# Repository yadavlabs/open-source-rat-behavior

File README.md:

# open-source-rat-behavior
Open source software for controlling operant conditioning chambers, running behavioral experiments, and collecting data. 

# IMPORTANT: This branch is a work in progress which now uses Docker for building and deploying the app. This README has not yet been updated to reflect these changes.

## Prerequisites
For specific version see `docs\Software Versions.xlsx`
- `Python` If using standalone [Python version](https://www.python.org/downloads/release/python-3810/), during installation check "Add python.exe to PATH"
- `Git` Can be downloaded from [here](https://git-scm.com/downloads/win)
- `Node.js` Can be downloaded from [here](https://nodejs.org/en/download). Do not check "Automatically install the necessary tools..."
- `Angular CLI`
    ```command
    >npm install -g @angular/cli@15.2.10
    >cd path\to\open-source-rat-behavior\Angular Files
    >ng add @angular/material
    ```

## Installation
1. Clone repository to your machine. 
2. Setup backend environment with `venv`
    - Choose or create a folder to store the environment
    - Open command terminal and run the following to create and activate the environment:
    ```command
    >cd path\to\open-source-rat-behavior\Flask Project Files\pythonBackend
    >python -m venv .venv
    >.venv\Scripts\activate.bat
    ```
    Note: While not necessary, it is best to have the environment folder in the `Flask Project Files\pythonBackend` directory and the environment named `.venv`

    - if the setup was successful, the command prompt will look like:
    ```command
    (.venv) C:\Users\...\open-source-rat-behavior>
    ```
    - (Optional) Upgrade pip and managing modules:
    ```command
    >python -m pip install --upgrade pip setuptools wheel
    ```
    - Install required modules in `requirements.txt` inside virtual environment:
    ```command
    >cd path\to\open-source-rat-behavior
    >pip install -r requirements.txt
    ```
    - To deactivate environment run:
    ```command
    >behavior-chamber-env\Scripts\deactivate.bat
    ```
    - Set name of Flask application (must be run on each usage unless `setx` is used):
    ```command
    >cd path\to\open-source-rat-behavior\Flask Project Files\pythonBackend
    >set FLASK_APP=application.py
    >set FLASK_DEBUG=true
    ```
3. Alternatively, setup backend environment with `conda`
    - In Anaconda Prompt:
    ```command
    >conda create -n behavior-chamber-env python=3.8
    >conda activate behavior-chamber-env
    >cd path\to\open-source-rat-behavior
    >pip install -r requirements.txt
    ```

## Launch Python Backend
1. Open command terminal.
2. Activate environment:
```command
>cd path\to\environment\folder
>behavior-chamber-env\Scripts\activate.bat
```
3. Navigate to the directory containing the file "application.py" and run app:
```command
>cd path\to\open-source-rat-behavior\Flask Project Files\pythonBackend
>flask run
```
Note: You don't need to open the URL (e.g. `http://127.0.0.1:5000`), but you can if you want

## Launch Angular App
1. Open a second command terminal.
2. Navigate to the diretory containing the folders "src", ".angular", etc. 
```command
>cd path\to\open-source-rat-behavior\Angular Files
```
3. Launch app:
```command
>ng serve --o
```
Note: The "--o" flag should open the application for you once it compiles. REMINDER THAT YOU NEED NODE.JS AND GIT INSTALLED, perhaps even Angular CLI.
You don't need Visual Studios unless you intend to modify code

## Launch Frontend and Backend with batch script
Instead of manually opening two terminals to start the app, two batch files are available to launch the frontend and backend automatically

1. `start-full.bat`
    - Run if the Python environment was setup with `venv`
    - Assumes the virtual environment is named `.venv` and is located in:
        `\Flask Project Files\pythonBackend\.venv`
    - If this is not the case update the following in the script:
        - `ENV_NAME`
        - `ENV_DIR`

2. `start-full-conda.bat`
    - Run if the Python environment was setup with `conda`
    - Assumes name of environment is `behavior-chamber-env` and Anaconda installation is `%USERPROFILE%\anaconda3\condabin\`
    - If this is not the case update the following in the script:
        - `ENV_NAME`
        - `ENV_DIR`

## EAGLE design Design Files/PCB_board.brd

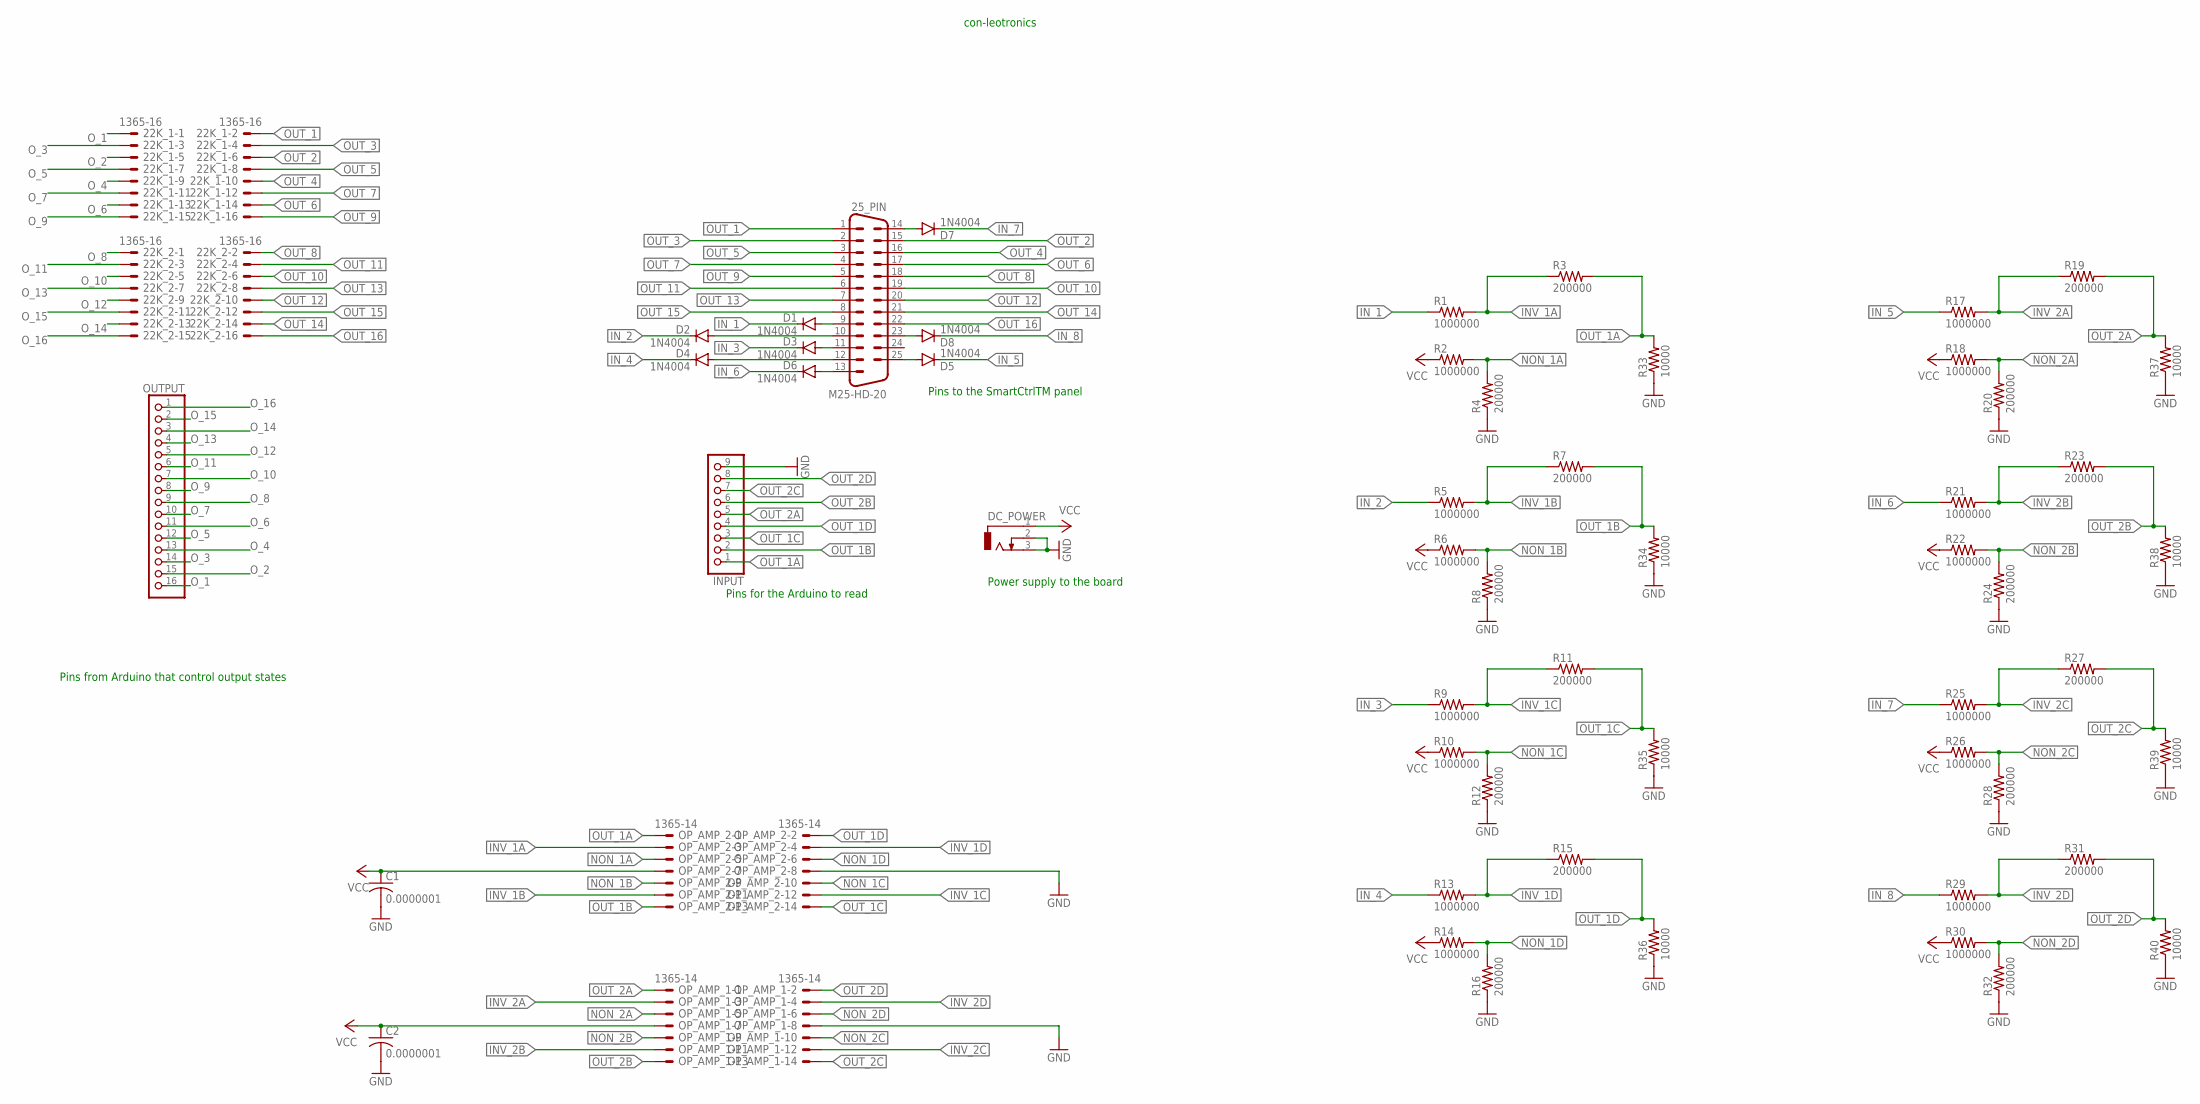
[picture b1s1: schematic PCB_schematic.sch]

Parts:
22K_1, 22K_2: 1365-16
25_PIN: M25-HD-20
C1, C2: 0.0000001; C1206
D1, D2, D3, D4, D5, D6, D7, D8: 1N4004; DO41-10
DC_POWER: DCJ0303
INPUT: PINHD-1X9; 1X09
OP_AMP_1, OP_AMP_2: 1365-14
OUTPUT: PINHD-1X16; 1X16
R1, R2, R5, R6, R9, R10, R13, R14, R17, R18, R21, R22, R25, R26, R29, R30: 1000000; R1206
R3, R4, R7, R8, R11, R12, R15, R16, R19, R20, R23, R24, R27, R28, R31, R32: 200000; R1206
R33, R34, R35, R36, R37, R38, R39, R40: 10000; R1206

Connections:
GND: C1.2, C2.2, DC_POWER.2, DC_POWER.3, INPUT.9, OP_AMP_1.8, OP_AMP_2.8, R4.1, R8.1, R12.1, R16.1, R20.1, R24.1, R28.1, R32.1, R33.1, R34.1, R35.1, R36.1, R37.1, R38.1, R39.1, R40.1
INV_1A: OP_AMP_2.3, R1.2, R3.1
INV_1B: OP_AMP_2.11, R5.2, R7.1
INV_1C: OP_AMP_2.12, R9.2, R11.1
INV_1D: OP_AMP_2.4, R13.2, R15.1
INV_2A: OP_AMP_1.3, R17.2, R19.1
INV_2B: OP_AMP_1.11, R21.2, R23.1
INV_2C: OP_AMP_1.12, R25.2, R27.1
INV_2D: OP_AMP_1.4, R29.2, R31.1
IN_1: D1.C, R1.1
IN_2: D2.C, R5.1
IN_3: D3.C, R9.1
IN_4: D4.C, R13.1
IN_5: D5.C, R17.1
IN_6: D6.C, R21.1
IN_7: D7.C, R25.1
IN_8: D8.C, R29.1
unnamed: 25_PIN.9, D1.A
unnamed: 25_PIN.10, D2.A
unnamed: 25_PIN.11, D3.A
unnamed: 25_PIN.12, D4.A
unnamed: 25_PIN.25, D5.A
unnamed: 25_PIN.13, D6.A
unnamed: 25_PIN.23, D8.A
unnamed: 25_PIN.14, D7.A
NON_1A: OP_AMP_2.5, R2.2, R4.2
NON_1B: OP_AMP_2.9, R6.2, R8.2
NON_1C: OP_AMP_2.10, R10.2, R12.2
NON_1D: OP_AMP_2.6, R14.2, R16.2
NON_2A: OP_AMP_1.5, R18.2, R20.2
NON_2B: OP_AMP_1.9, R22.2, R24.2
NON_2C: OP_AMP_1.10, R26.2, R28.2
NON_2D: OP_AMP_1.6, R30.2, R32.2
OUT_1: 22K_1.2, 25_PIN.1
OUT_1A: INPUT.1, OP_AMP_2.1, R3.2, R33.2
OUT_1B: INPUT.2, OP_AMP_2.13, R7.2, R34.2
OUT_1C: INPUT.3, OP_AMP_2.14, R11.2, R35.2
OUT_1D: INPUT.4, OP_AMP_2.2, R15.2, R36.2
OUT_2: 22K_1.6, 25_PIN.15
OUT_2A: INPUT.5, OP_AMP_1.1, R19.2, R37.2
OUT_2B: INPUT.6, OP_AMP_1.13, R23.2, R38.2
OUT_2C: INPUT.7, OP_AMP_1.14, R27.2, R39.2
OUT_2D: INPUT.8, OP_AMP_1.2, R31.2, R40.2
OUT_3: 22K_1.4, 25_PIN.2
OUT_4: 22K_1.10, 25_PIN.16
OUT_5: 22K_1.8, 25_PIN.3
OUT_6: 22K_1.14, 25_PIN.17
OUT_7: 22K_1.12, 25_PIN.4
OUT_8: 22K_2.2, 25_PIN.18
OUT_9: 22K_1.16, 25_PIN.5
OUT_10: 22K_2.6, 25_PIN.19
OUT_11: 22K_2.4, 25_PIN.6
OUT_12: 22K_2.10, 25_PIN.20
OUT_13: 22K_2.8, 25_PIN.7
OUT_14: 22K_2.14, 25_PIN.21
OUT_15: 22K_2.12, 25_PIN.8
OUT_16: 22K_2.16, 25_PIN.22
O_1: 22K_1.1, OUTPUT.16
O_2: 22K_1.5, OUTPUT.15
O_3: 22K_1.3, OUTPUT.14
O_4: 22K_1.9, OUTPUT.13
O_5: 22K_1.7, OUTPUT.12
O_6: 22K_1.13, OUTPUT.11
O_7: 22K_1.11, OUTPUT.10
O_8: 22K_2.1, OUTPUT.9
O_9: 22K_1.15, OUTPUT.8
O_10: 22K_2.5, OUTPUT.7
O_11: 22K_2.3, OUTPUT.6
O_12: 22K_2.9, OUTPUT.5
O_13: 22K_2.7, OUTPUT.4
O_14: 22K_2.13, OUTPUT.3
O_15: 22K_2.11, OUTPUT.2
O_16: 22K_2.15, OUTPUT.1
VCC: C1.1, C2.1, DC_POWER.1, OP_AMP_1.7, OP_AMP_2.7, R2.1, R6.1, R10.1, R14.1, R18.1, R22.1, R26.1, R30.1

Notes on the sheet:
Pins for the Arduino to read
Power supply to the board
Pins to the SmartCtrlTM panel
con-leotronics
Pins from Arduino that control output states

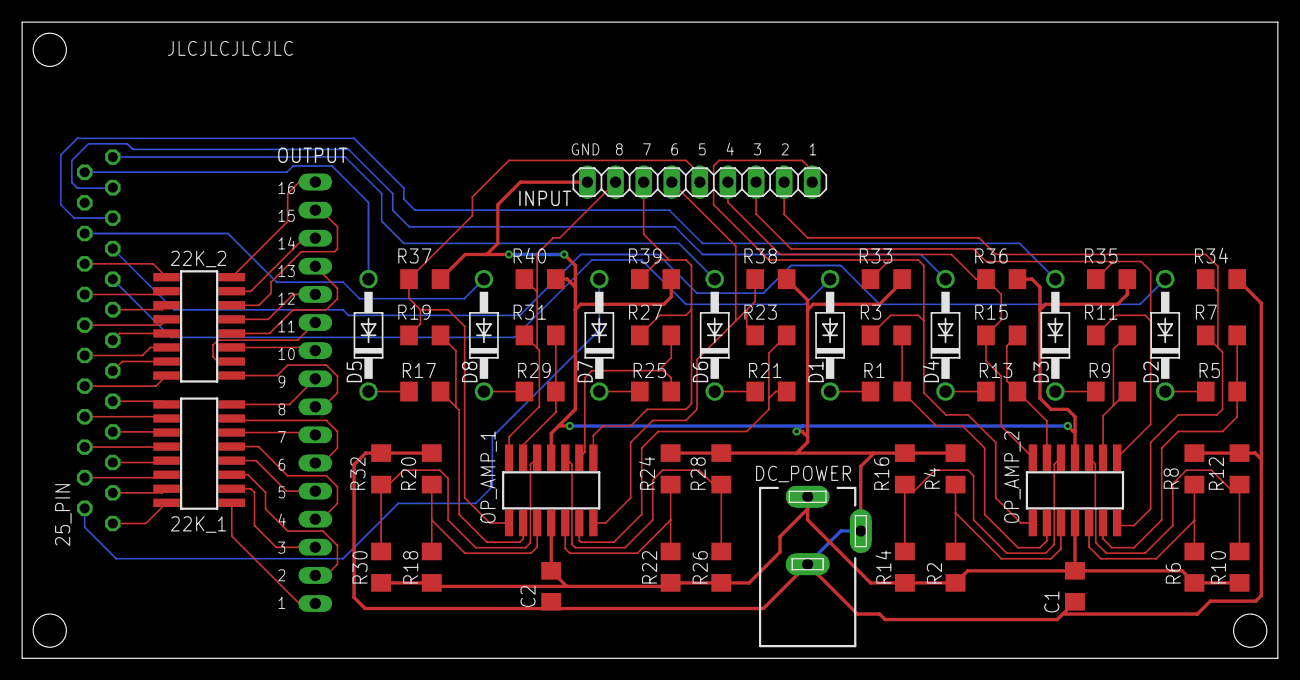
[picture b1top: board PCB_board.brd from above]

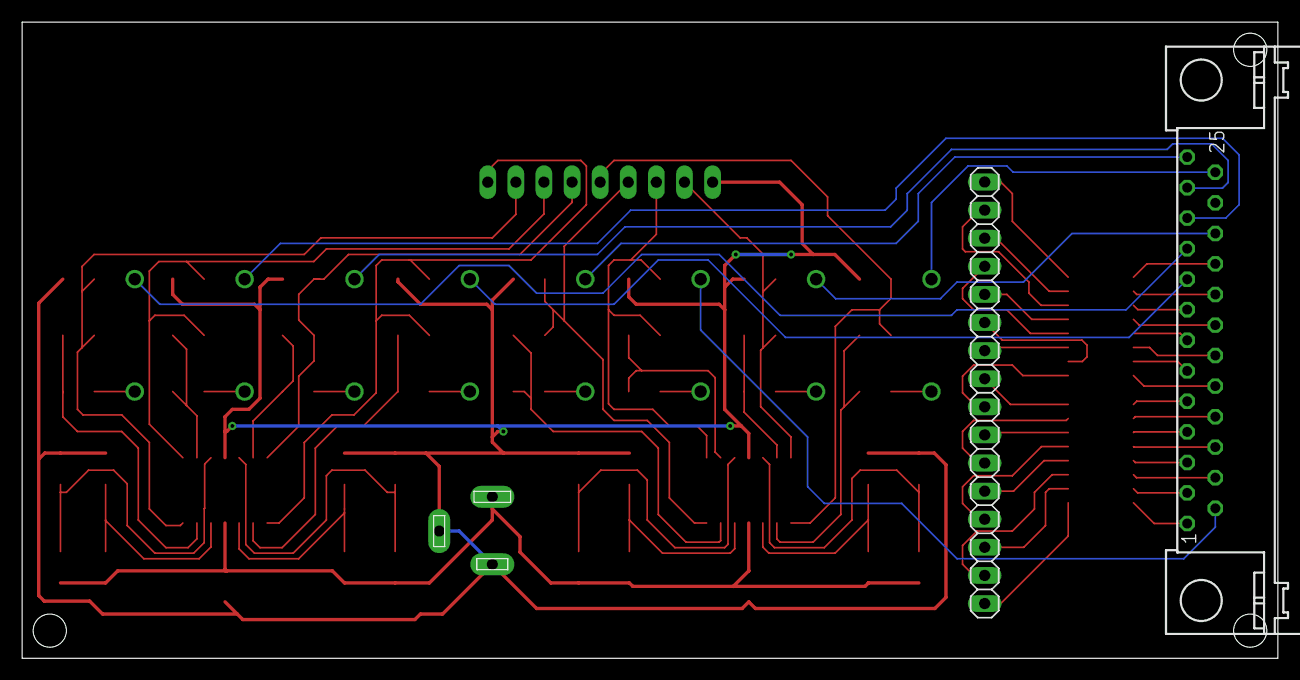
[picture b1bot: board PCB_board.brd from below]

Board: 2 copper layers, 113.5 x 57.5 mm, 58 parts (2 on the bottom side), 74 nets.

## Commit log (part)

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2025-02-18 Added all files to repo
2025-02-18 Create LICENSE
2025-03-10 Added rat data to repo
2025-03-11 Added scripts for plotting Figure 6
2025-07-10 Software Versions.xlsx incorrectly listed the python version and is now fixed.
2025-07-14 Added batch file to start both frontend and backend automactically
2025-07-14 Added batch files for automatically running frontend and backend. Updated README and verified a few python/package versioning requirements.
2025-07-15 Small edits to app button enable/disable logic
2025-07-16 Added branch for auditory experiment
2025-07-24 Updates to auditory discrimination task
2025-07-25 Added branch for working on thread-based arduino listener
2025-07-29 More work on thread-based version
2025-07-31 Further integration of thread-based arduino listener.
2025-08-01 Save data functionality updated and bug fixes
2025-08-01 Bug fixes
2025-08-05 Fixed bug in auditory detection, updated save data feature
2025-10-17 Pushing last change to arduino code for paper
2025-10-17 commented out/removed some debugging print/log statements
2025-10-28 Added sequence diagram of full stack component interactions
2025-11-04 Added PDF of schematic for visualization.
2025-11-18 Added PDF of PCB schematic
2025-11-24 Updated gitignore in serial-thread-dev and removed old data
2025-11-24 Updated gitignore and removed old data
2026-05-08 Updates for 5/7/26 submission. docs/User Manual.docx now indcludes additional detail regarding hardware setup. Added docs/GUI Screenshots with Terminal Outputs.png.
2026-05-14 First commit for vibration stimulus experiments. New branch for working on it.
2026-05-15 Added parameter randomization and save/load functionality for controlling and keeping track of stimulus randomization across sessions.
2026-06-17 Changes to box-specific settings in arduino code
2026-06-17 Added randomization for vibration stimulus parameters.
2026-06-19 Restructuring/renaming directories for improved organization to streamline developing. Started work testing out using docker to handle everything. This would specifically remove the need to install n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
2026-06-19 Batch file now properly runs app and proxy server. Currenty testing seems that everything is working besides importing and exporting parameters. Major rework to exporting/saving session data. This is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
2026-06-19 Work on integrating xipppy into docker for controlling Ripple Stimulator
2026-06-24 Xipppy now integrated in class. Still testing but works well so far.
2026-06-25 Reworked front end initialization and handling of stimulation parameters. Form fields are now generated with ngFor based on a key-value datatype that holds all parameters. Made other updates regardin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
